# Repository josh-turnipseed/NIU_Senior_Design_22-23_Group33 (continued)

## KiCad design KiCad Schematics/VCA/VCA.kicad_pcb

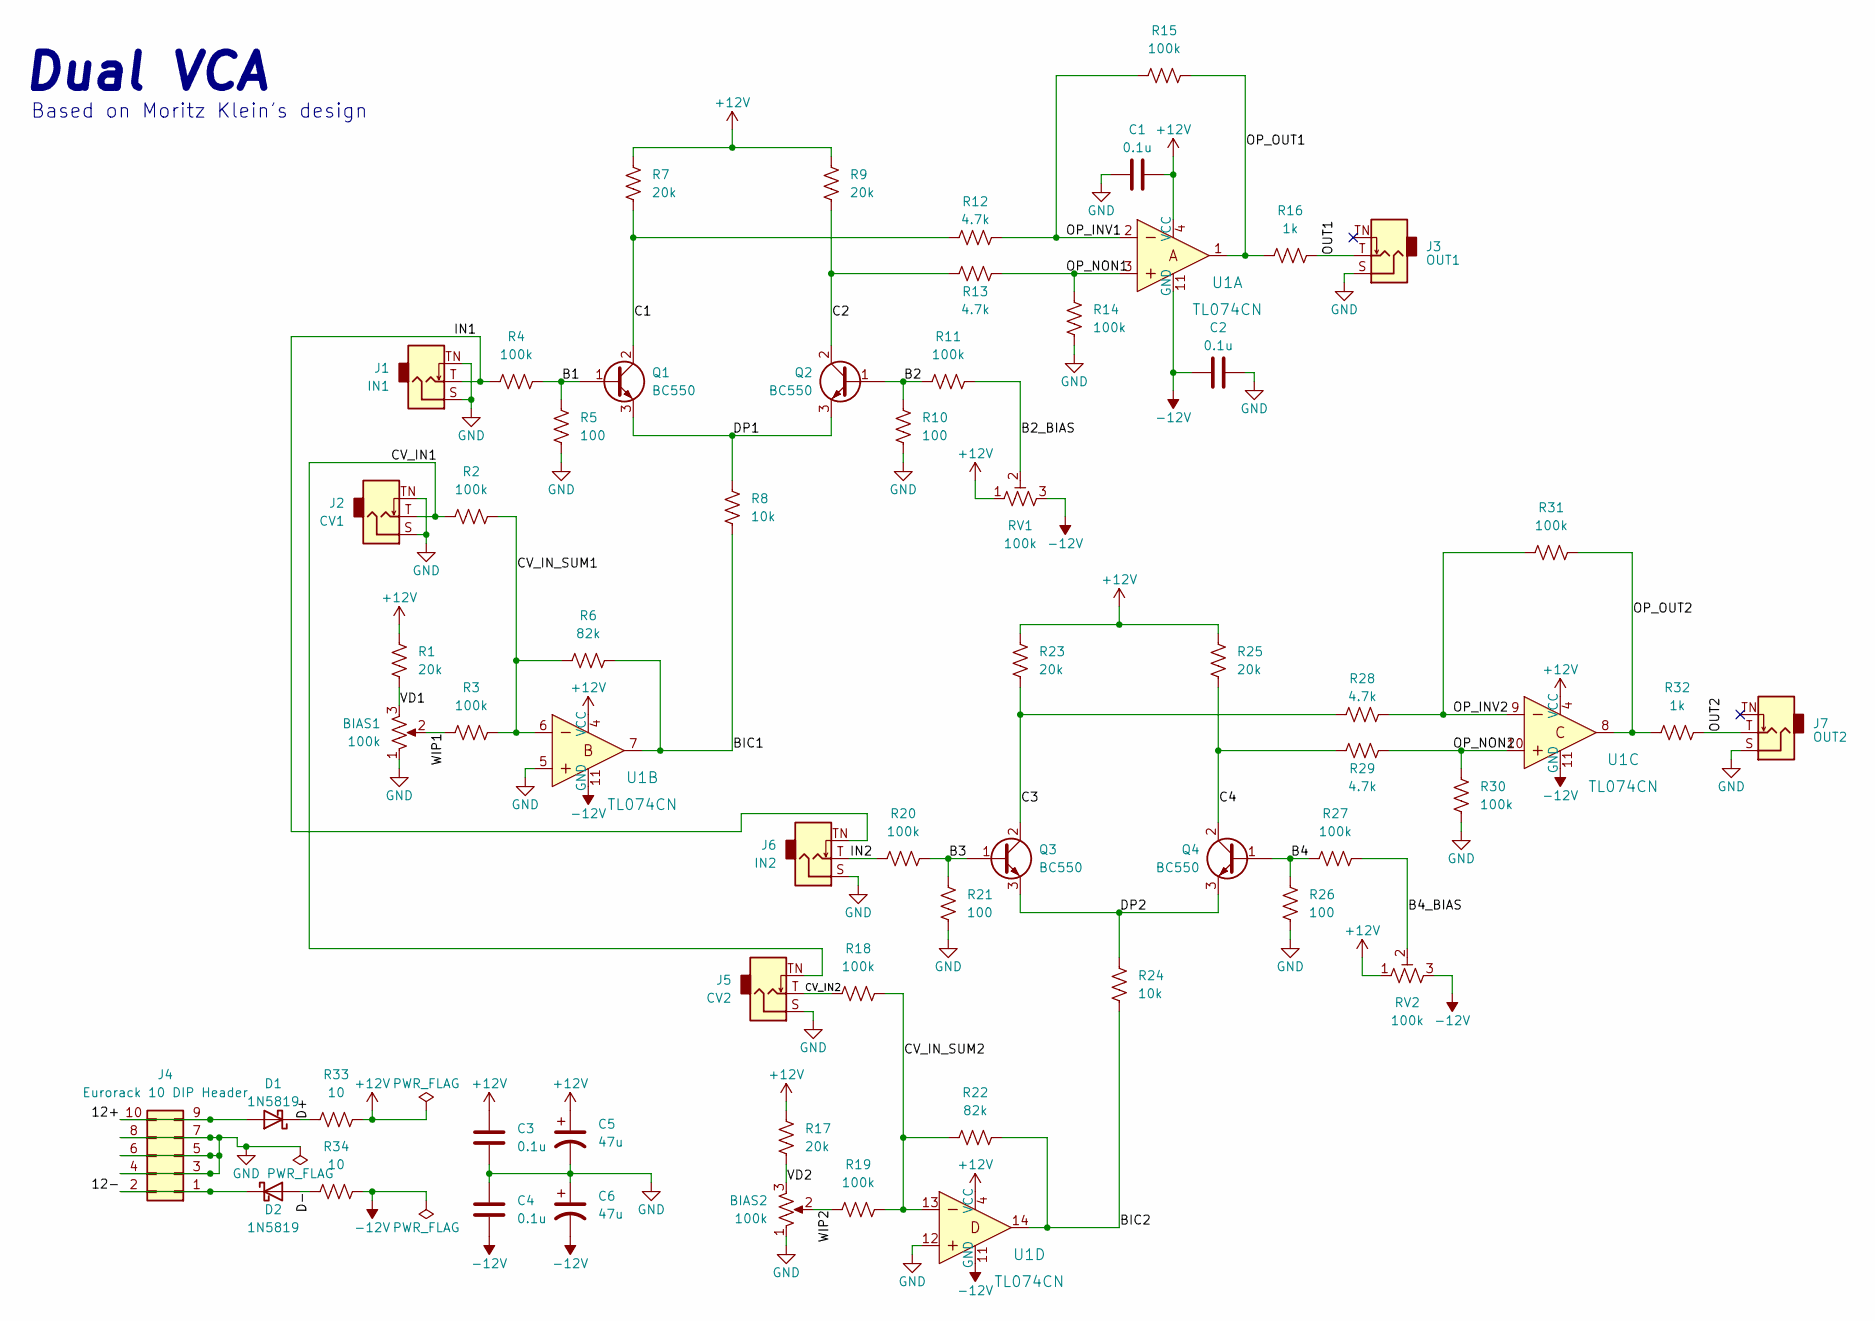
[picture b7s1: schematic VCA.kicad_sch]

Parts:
BIAS1, BIAS2: 100k; Alpha_9mm_Potentiometer_Aligned
C1, C2, C3, C4: 0.1u; C_Disc_D4.7mm_W2.5mm_P5.00mm
C5, C6: 47u; CP_Radial_D4.0mm_P2.00mm
D1, D2: 1N5819; D_DO-41_SOD81_P10.16mm_Horizontal
J1: IN1; Jack_3.5mm_QingPu_WQP-PJ398SM_Vertical_CircularHoles
J2: CV1; Jack_3.5mm_QingPu_WQP-PJ398SM_Vertical_CircularHoles
J3: OUT1; Jack_3.5mm_QingPu_WQP-PJ398SM_Vertical_CircularHoles
J4: Eurorack 10 DIP Header; Eurorack_10_pin_header
J5: CV2; Jack_3.5mm_QingPu_WQP-PJ398SM_Vertical_CircularHoles
J6: IN2; Jack_3.5mm_QingPu_WQP-PJ398SM_Vertical_CircularHoles
J7: OUT2; Jack_3.5mm_QingPu_WQP-PJ398SM_Vertical_CircularHoles
Q1, Q2, Q3, Q4: BC550; TO-92L_Inline_Wide
R1, R7, R9, R17, R23, R25: 20k; R_Axial_DIN0207_L6.3mm_D2.5mm_P2.54mm_Vertical
R2, R3, R4, R11, R14, R15, R18, R19, R20, R27, R30, R31: 100k; R_Axial_DIN0207_L6.3mm_D2.5mm_P2.54mm_Vertical
R5, R10, R21, R26: 100; R_Axial_DIN0207_L6.3mm_D2.5mm_P2.54mm_Vertical
R6, R22: 82k; R_Axial_DIN0207_L6.3mm_D2.5mm_P2.54mm_Vertical
R8, R24: 10k; R_Axial_DIN0207_L6.3mm_D2.5mm_P2.54mm_Vertical
R12, R13, R28, R29: 4.7k; R_Axial_DIN0207_L6.3mm_D2.5mm_P2.54mm_Vertical
R16, R32: 1k; R_Axial_DIN0207_L6.3mm_D2.5mm_P2.54mm_Vertical
R33, R34: 10; R_Axial_DIN0207_L6.3mm_D2.5mm_P7.62mm_Horizontal
RV1, RV2: 100k; 3296Y1502LF
U1: TL074CN; DIP-14_W3mm; MPN TL074CN

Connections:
+12V: C1.2, C3.2, C5.1, R1.2, R7.1, R9.1, R17.2, R23.1, R25.1, R33.1, RV1.1, RV2.1, U1.4 (VCC)
-12V: C2.1, C4.1, C6.2, R34.1, RV1.3, RV2.3, U1.11 (GND)
/12+: D1.2 (A), J4.9, J4.10
/12-: D2.1 (K), J4.1, J4.2
/B1: Q1.1 (B), R4.2, R5.1
/B2: Q2.1 (B), R10.1, R11.1
/B2_BIAS: R11.2, RV1.2
/B3: Q3.1 (B), R20.2, R21.1
/B4: Q4.1 (B), R26.1, R27.1
/B4_BIAS: R27.2, RV2.2
/BIC1: R6.2, R8.2, U1.7
/BIC2: R22.2, R24.2, U1.14
/C1: Q1.2 (C), R7.2, R12.1
/C2: Q2.2 (C), R9.2, R13.1
/C3: Q3.2 (C), R23.2, R28.1
/C4: Q4.2 (C), R25.2, R29.1
/CV_IN1: J2.T, J5.TN, R2.1
/CV_IN2: J5.T, R18.1
/CV_IN_SUM1: R2.2, R3.2, R6.1, U1.6
/CV_IN_SUM2: R18.2, R19.2, R22.1, U1.13
/D+: D1.1 (K), R33.2
/D-: D2.2 (A), R34.2
/DP1: Q1.3 (E), Q2.3 (E), R8.1
/DP2: Q3.3 (E), Q4.3 (E), R24.1
/IN1: J1.T, J6.TN, R4.1
/IN2: J6.T, R20.1
/OP_INV1: R12.2, R15.1, U1.2
/OP_INV2: R28.2, R31.1, U1.9
/OP_NON1: R13.2, R14.2, U1.3
/OP_NON2: R29.2, R30.2, U1.10
/OP_OUT1: R15.2, R16.1, U1.1
/OP_OUT2: R31.2, R32.1, U1.8
/OUT1: J3.T, R16.2
/OUT2: J7.T, R32.2
/VD1: BIAS1.3, R1.1
/VD2: BIAS2.3, R17.1
/WIP1: BIAS1.2, R3.1
/WIP2: BIAS2.2, R19.1
GND: BIAS1.1, BIAS2.1, C1.1, C2.2, C3.1, C4.2, C5.2, C6.1, J1.S, J1.TN, J2.S, J2.TN, J3.S, J4.3, J4.4, J4.5, J4.6, J4.7, J4.8, J5.S, J6.S, J7.S, R5.2, R10.2, R14.1, R21.2, R26.2, R30.1, U1.5, U1.12

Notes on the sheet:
Based on Moritz Klein's design
Dual VCA

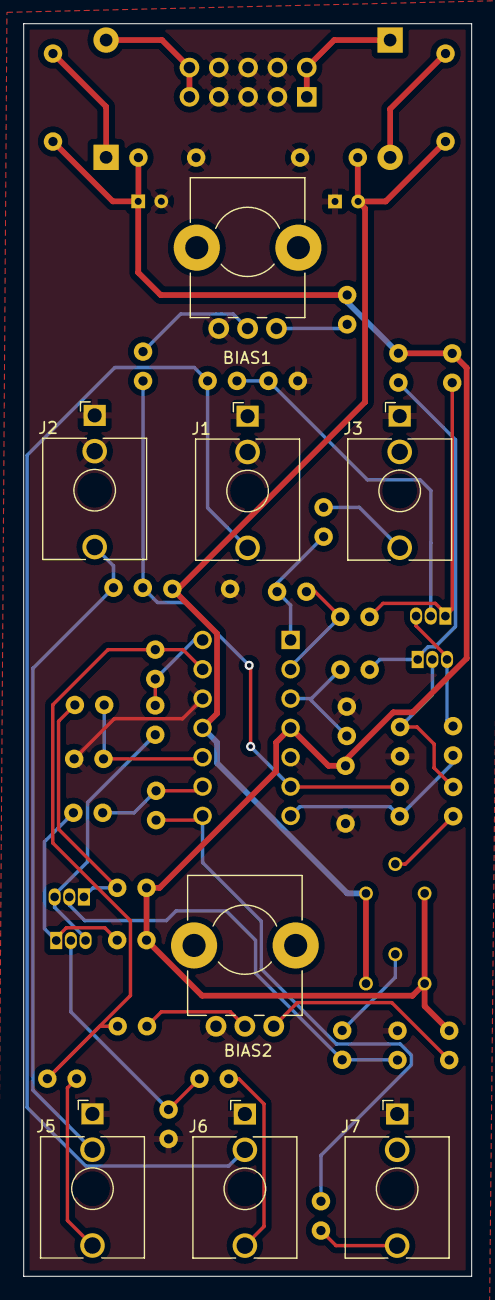
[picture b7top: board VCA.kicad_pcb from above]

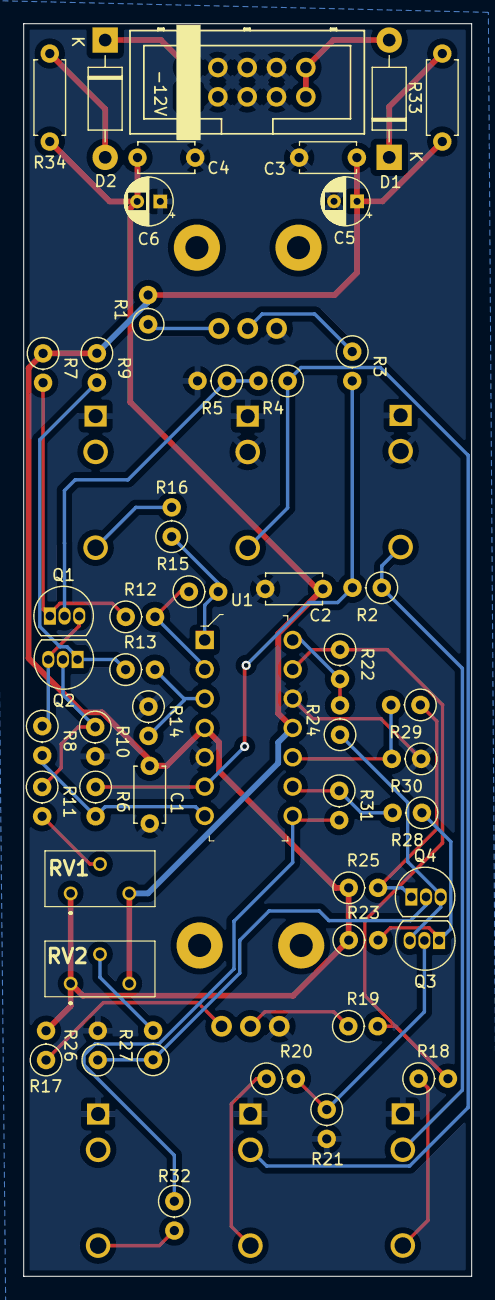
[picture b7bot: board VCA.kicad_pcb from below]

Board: 2 copper layers, 38.8 x 108.5 mm, 58 parts (50 on the bottom side), 39 nets.

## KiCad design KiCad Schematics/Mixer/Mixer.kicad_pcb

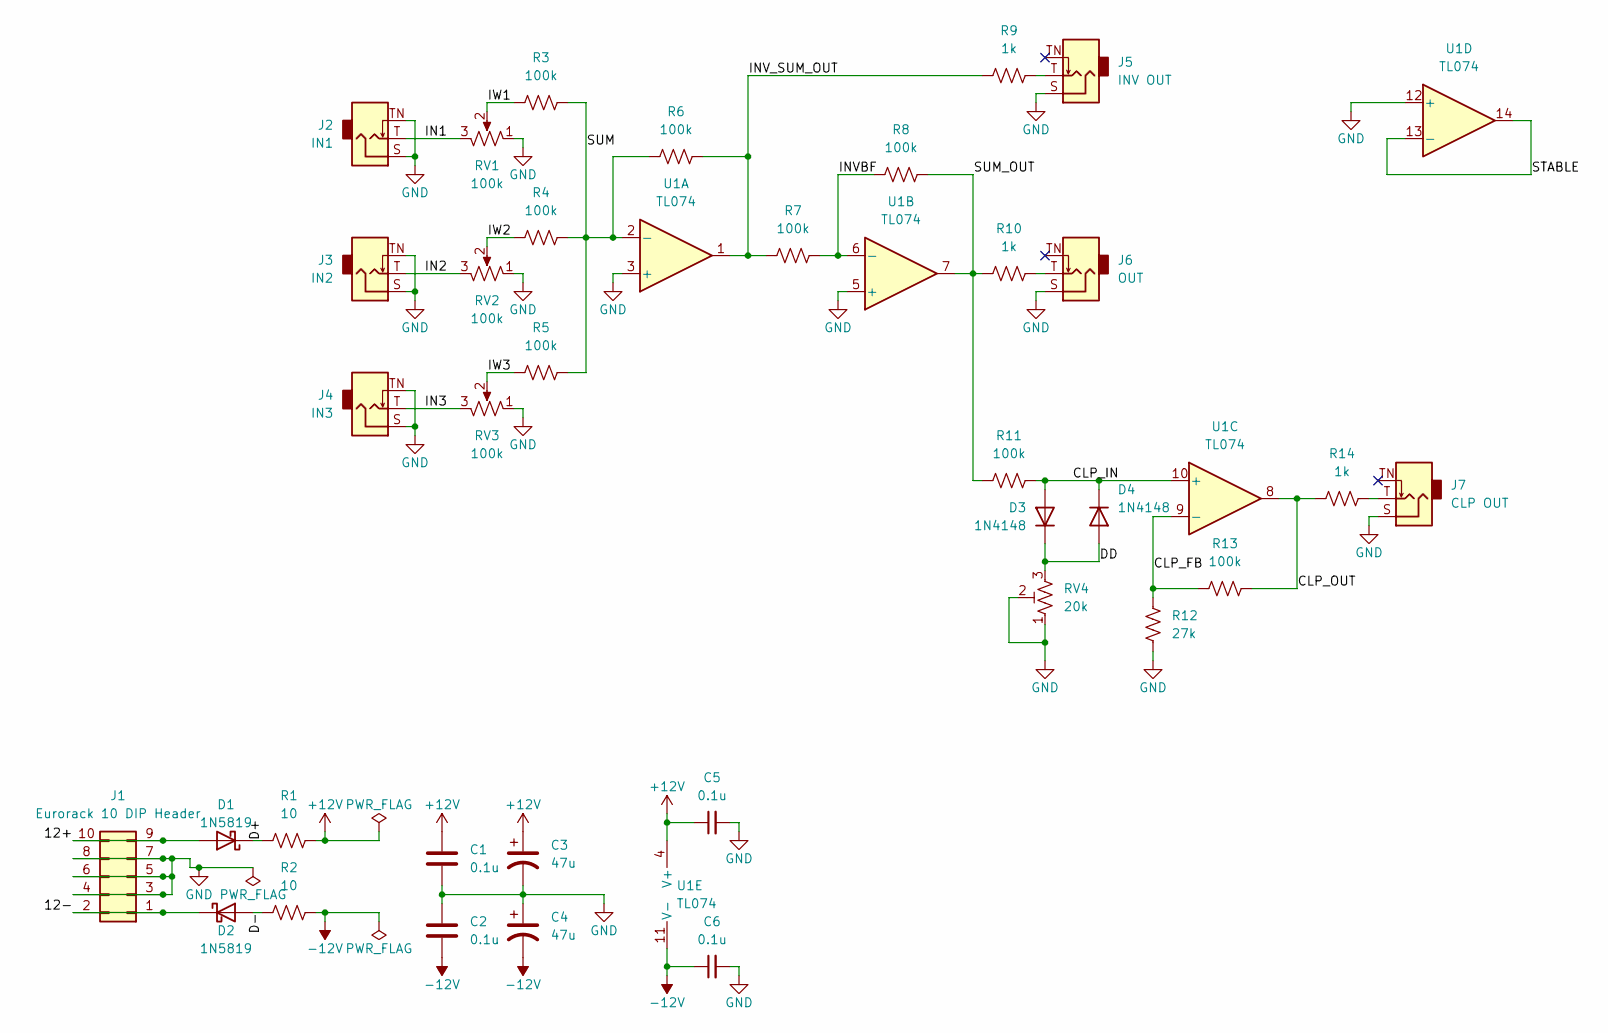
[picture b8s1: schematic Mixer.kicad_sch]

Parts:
C1, C2, C5, C6: 0.1u; C_Disc_D4.7mm_W2.5mm_P5.00mm
C3, C4: 47u; CP_Radial_D4.0mm_P2.00mm
D1, D2: 1N5819; D_DO-41_SOD81_P3.81mm_Vertical_KathodeUp
D3, D4: 1N4148; D_DO-41_SOD81_P2.54mm_Vertical_KathodeUp
J1: Eurorack 10 DIP Header; Eurorack_10_pin_header
J2: IN1; Jack_3.5mm_QingPu_WQP-PJ398SM_Vertical_CircularHoles
J3: IN2; Jack_3.5mm_QingPu_WQP-PJ398SM_Vertical_CircularHoles
J4: IN3; Jack_3.5mm_QingPu_WQP-PJ398SM_Vertical_CircularHoles
J5: INV OUT; Jack_3.5mm_QingPu_WQP-PJ398SM_Vertical_CircularHoles
J6: OUT; Jack_3.5mm_QingPu_WQP-PJ398SM_Vertical_CircularHoles
J7: CLP OUT; Jack_3.5mm_QingPu_WQP-PJ398SM_Vertical_CircularHoles
R1, R2: 10; R_Axial_DIN0207_L6.3mm_D2.5mm_P2.54mm_Vertical
R3, R4, R5, R6, R7, R8, R11, R13: 100k; R_Axial_DIN0207_L6.3mm_D2.5mm_P2.54mm_Vertical
R9, R10, R14: 1k; R_Axial_DIN0207_L6.3mm_D2.5mm_P2.54mm_Vertical
R12: 27k; R_Axial_DIN0207_L6.3mm_D2.5mm_P2.54mm_Vertical
RV1, RV2, RV3: 100k; Alpha_9mm_Potentiometer_Aligned
RV4: 20k; 3296Y1104LF
U1: TL074; DIP-14_W7.62mm

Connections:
+12V: C1.2, C3.1, C5.1, R1.1, U1.4 (V+)
-12V: C2.1, C4.2, C6.1, R2.1, U1.11 (V-)
/12+: D1.2 (A), J1.9, J1.10
/12-: D2.1 (K), J1.1, J1.2
/CLP_FB: R12.2, R13.1, U1.9 (-)
/CLP_IN: D3.2 (A), D4.1 (K), R11.2, U1.10 (+)
/CLP_OUT: R13.2, R14.1, U1.8
/D+: D1.1 (K), R1.2
/D-: D2.2 (A), R2.2
/DD: D3.1 (K), D4.2 (A), RV4.3
/IN1: J2.T, RV1.3
/IN2: J3.T, RV2.3
/IN3: J4.T, RV3.3
/INVBF: R7.2, R8.1, U1.6 (-)
/INV_SUM_OUT: R6.2, R7.1, R9.1, U1.1
/IW1: R3.1, RV1.2
/IW2: R4.1, RV2.2
/IW3: R5.1, RV3.2
/STABLE: U1.13 (-), U1.14
/SUM: R3.2, R4.2, R5.2, R6.1, U1.2 (-)
/SUM_OUT: R8.2, R10.1, R11.1, U1.7
GND: C1.1, C2.2, C3.2, C4.1, C5.2, C6.2, J1.3, J1.4, J1.5, J1.6, J1.7, J1.8, J2.S, J2.TN, J3.S, J3.TN, J4.S, J4.TN, J5.S, J6.S, J7.S, R12.1, RV1.1, RV2.1, RV3.1, RV4.1, RV4.2, U1.3 (+), U1.5 (+), U1.12 (+)
unnamed: J5.T, R9.2
unnamed: J6.T, R10.2
unnamed: J7.T, R14.2

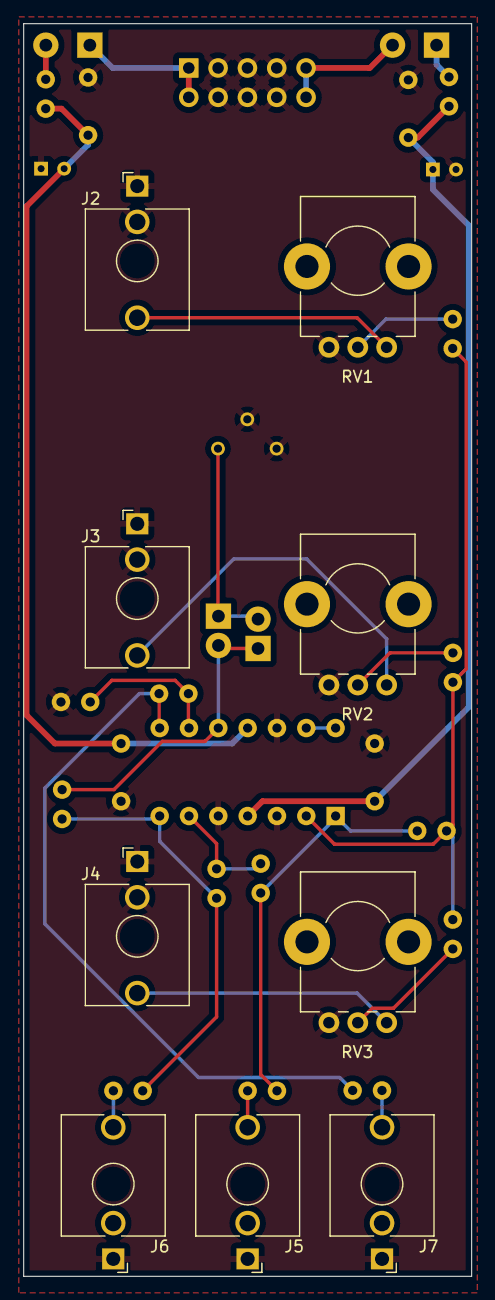
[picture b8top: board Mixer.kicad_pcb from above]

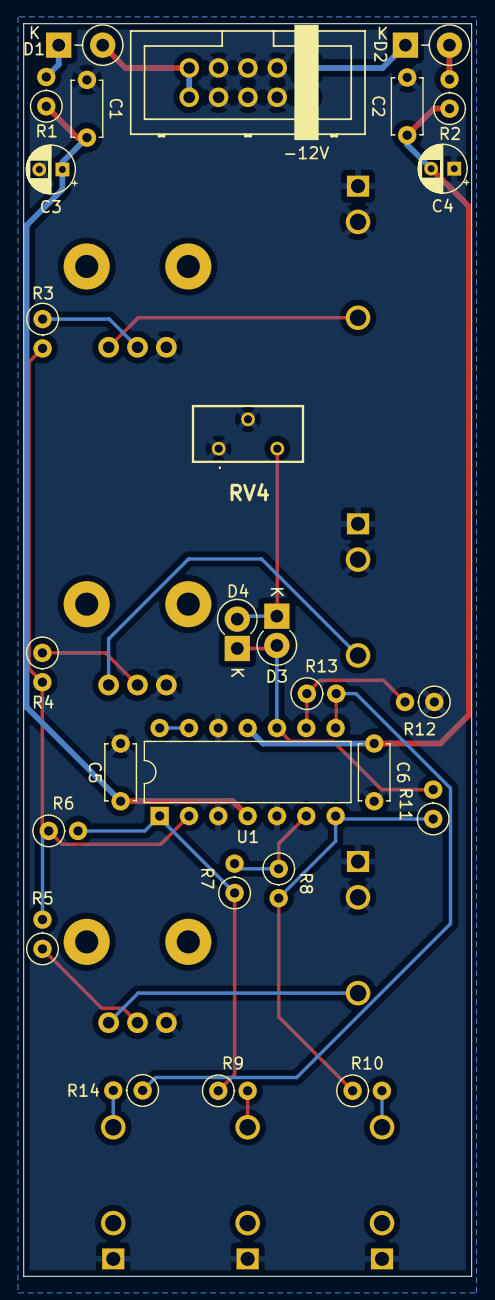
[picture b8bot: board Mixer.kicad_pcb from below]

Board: 2 copper layers, 38.8 x 108.5 mm, 36 parts (27 on the bottom side), 25 nets.

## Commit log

2023-05-11 Added schematic files
2023-05-11 Added symbol, footprint, and template files
2023-05-11 Added step files
2023-05-12 Added pictures
2023-05-12 Added Gcode files
2023-05-12 Renamed picture files
2023-05-12 Added Abstract file
